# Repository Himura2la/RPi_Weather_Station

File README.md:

# Raspberry Pi Weather Station
The online weather station based on Raspberry Pi

## Version 2.0

It includes three sensors.

* DS18B20 - to monitor temperature outside
* BMP085 - to monitor atmospheric pressure and temperature once again (it can be put to another place)
* TSL2561 - to monitor the lightness. Nobody measures the lightness! I'll be the first! Why not?
* DHT22 - to monitor humidity and temeperature at the attic.

The library for TSL2561 was written from scratch based on the [official Adafruit library](https://github.com/adafruit/TSL2561-Arduino-Library) and the [official datasheet](http://www.adafruit.com/datasheets/TSL2561.pdf). Not all features are implemented (consider pull request?), but at least it gives the correct measurements in lux with the clear code for Python 2 (not just like [this](https://github.com/seanbechhofer/raspberrypi/blob/master/python/TSL2561.py) or [this](https://github.com/janheise/TSL2561))

## Version 1.0
Was working for about three months. It has had only one sensor BMP085 which were collecting pressure and temperature to the MySQL database. 
The back-end was implementen in Python, the front-end -- in [DevExpress JS controls](http://js.devexpress.com/).

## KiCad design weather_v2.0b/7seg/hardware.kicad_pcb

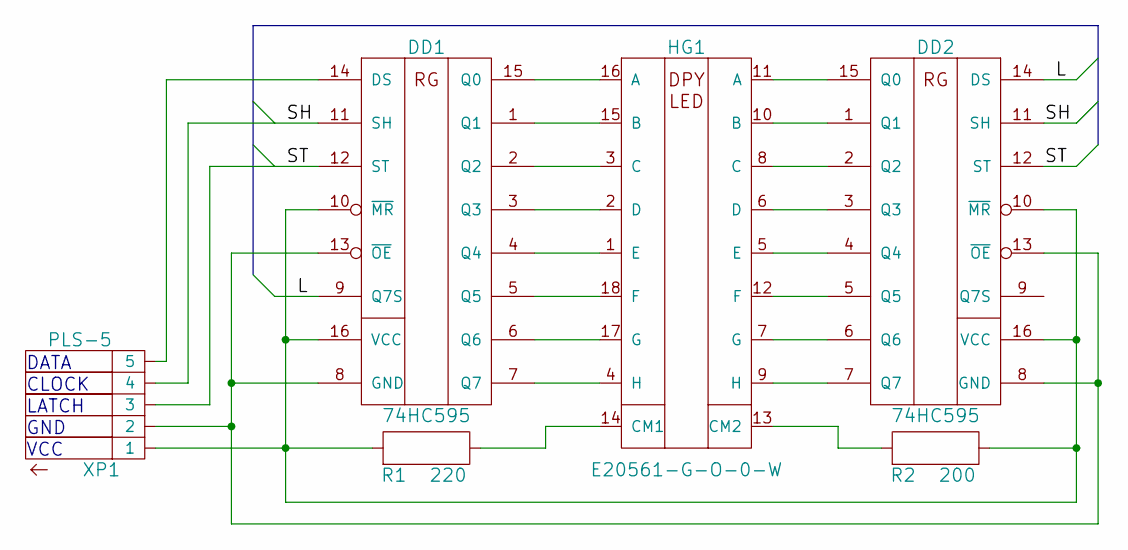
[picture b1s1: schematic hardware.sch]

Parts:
DD1, DD2: 74HC595
HG1: E20561-G-O-0-W
R1: 220
R2: 200
XP1: PLS-5

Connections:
/L: DD1.9 (Q7S), DD2.14 (DS)
/SH: DD1.11 (SH), DD2.11 (SH), XP1.4
/ST: DD1.12 (ST), DD2.12 (ST), XP1.3
unnamed: HG1.14 (CM1), R1.2
unnamed: DD1.10 (~MR), DD1.16 (VCC), DD2.10 (~MR), DD2.16 (VCC), R1.1, R2.2, XP1.1
unnamed: HG1.13 (CM2), R2.1
unnamed: DD2.7 (Q7), HG1.9 (H)
unnamed: DD2.6 (Q6), HG1.7 (G)
unnamed: DD2.5 (Q5), HG1.12 (F)
unnamed: DD2.4 (Q4), HG1.5 (E)
unnamed: DD2.3 (Q3), HG1.6 (D)
unnamed: DD2.2 (Q2), HG1.8 (C)
unnamed: DD2.1 (Q1), HG1.10 (B)
unnamed: DD2.15 (Q0), HG1.11 (A)
unnamed: DD1.7 (Q7), HG1.4 (H)
unnamed: DD1.6 (Q6), HG1.17 (G)
unnamed: DD1.5 (Q5), HG1.18 (F)
unnamed: DD1.4 (Q4), HG1.1 (E)
unnamed: DD1.14 (DS), XP1.5
unnamed: DD1.8 (GND), DD1.13 (~OE), DD2.8 (GND), DD2.13 (~OE), XP1.2
unnamed: DD1.3 (Q3), HG1.2 (D)
unnamed: DD1.15 (Q0), HG1.16 (A)
unnamed: DD1.1 (Q1), HG1.15 (B)
unnamed: DD1.2 (Q2), HG1.3 (C)

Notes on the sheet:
VCC
GND
LATCH
CLOCK
DATA

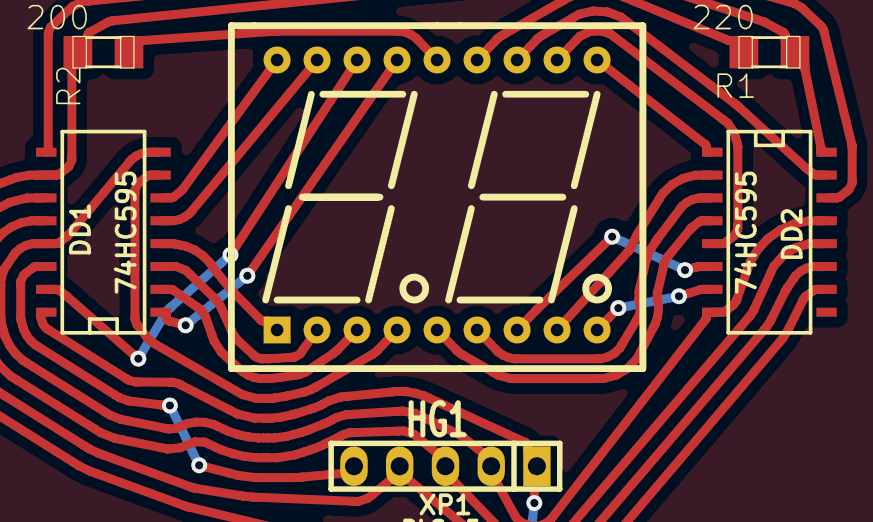
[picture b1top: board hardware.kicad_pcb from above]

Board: 2 copper layers, 6 parts (0 on the bottom side), 24 nets.

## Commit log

2015-04-05 :octocat: Added .gitattributes
2015-04-05 Enter
2015-04-05 Useful files
2015-04-10 alpha
2015-04-10 Hardware design
2015-04-25 bugfix
2015-06-06 15.1 controls
    good normal pressure
    get.py improved
2015-06-07 7seg made
2015-06-17 sample data
2015-06-29 release of v2
2015-06-29 add readme to c code
2015-06-29 cleanup
2015-06-29 cleanup [2]
2015-06-29 cleanup [3]
2015-06-29 updated desc
2015-07-06 added install instructions
2015-08-14 narodmon
2015-08-14 removed v1
2015-08-14 config updated
2015-08-15 rpi config update
2015-08-15 relative path
2015-08-15 one more installation
2015-09-06 the last commit
2015-09-06 cleaning db-related stuff
2017-11-16 not under development
